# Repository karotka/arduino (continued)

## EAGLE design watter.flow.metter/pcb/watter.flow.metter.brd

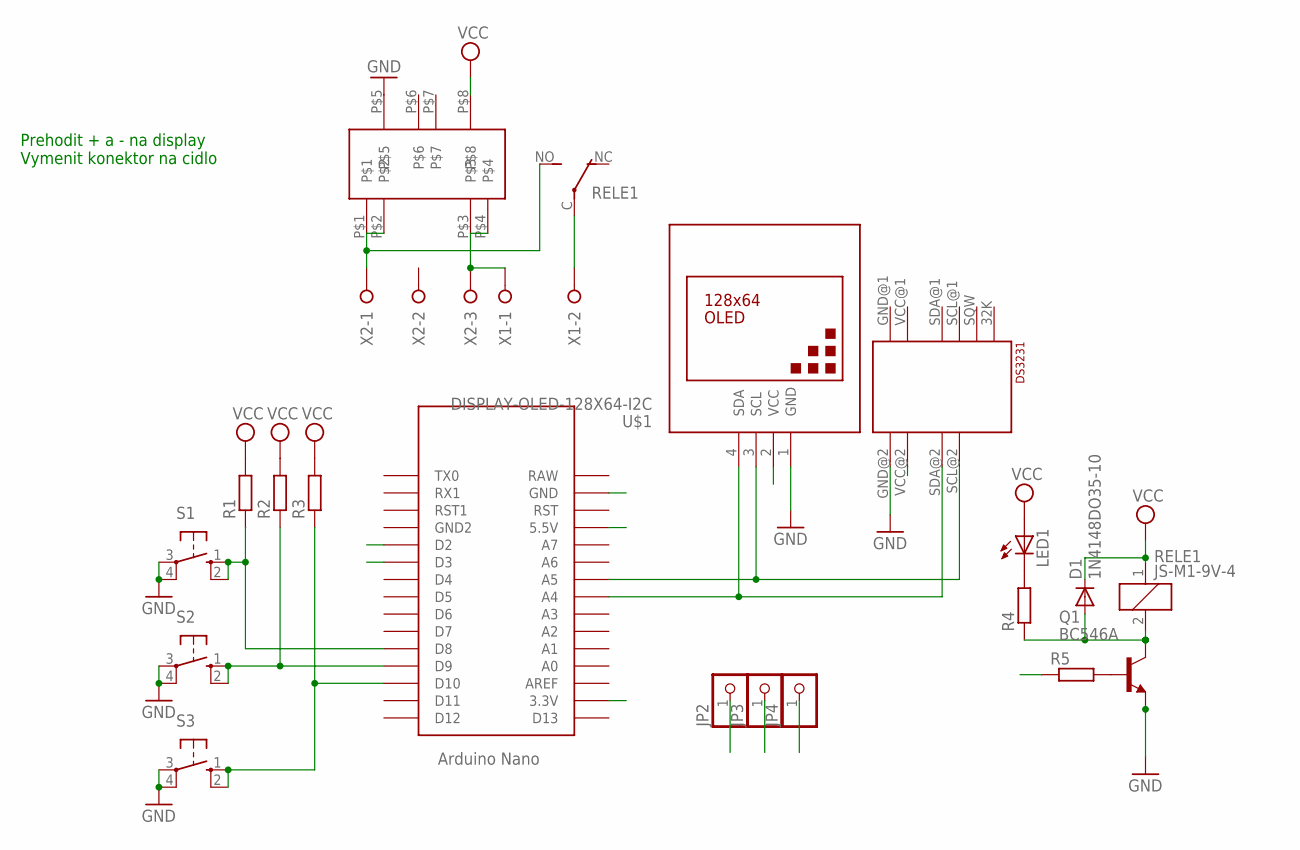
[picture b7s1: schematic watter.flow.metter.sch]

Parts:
D1: 1N4148DO35-10; DO35-10
JP2, JP3, JP4: PINHD-1X1; 1X01
LED1: LED3MM
Q1: BC546A; TO92-EBC
R1, R2, R3, R4: R-EU_0207/10; 0207/10
R5: R-EU_0207/15; 0207/15
RELE1: JS-M1-9V-4; JS-M
S1, S2, S3: 10-XX; B3F-10XX
U$1: DISPLAY-OLED-128X64-I2C
U$2: PWR5V; SUPP
U$5: NANO
U$6: DS3231BOARD; BOARD
X1: W237-02P; W237-132
X2: W237-3E

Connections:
3.3V: U$1.2 (VCC), U$5.3.3V, U$6.VCC@2 (VCC)
D2: JP3.1, U$5.D2
D3: R5.1, U$5.D3
GND: JP4.1, Q1.E, S1.3, S1.4 (P1), S2.3, S2.4 (P1), S3.3, S3.4 (P1), U$1.1 (GND), U$2.P$5, U$5.GND, U$6.GND@1 (GND), U$6.GND@2 (GND)
unnamed: RELE1.C, X1.2
unnamed: R1.1, S1.1 (S), S1.2 (S1), U$5.D8
unnamed: U$2.P$3, U$2.P$4, X1.1, X2.3
unnamed: RELE1.NO (S), U$2.P$1, U$2.P$2, X2.1
unnamed: R2.1, S2.1 (S), S2.2 (S1), U$5.D9
unnamed: R3.1, S3.1 (S), S3.2 (S1), U$5.D10
unnamed: Q1.B, R5.2
unnamed: LED1.K (C), R4.2
unnamed: D1.A, Q1.C, R4.1, RELE1.2
SCL: U$1.3 (SCL), U$5.A5, U$6.SCL@2 (SCL)
SDA: U$1.4 (SDA), U$5.A4, U$6.SDA@2 (SDA)
VCC: D1.C, JP2.1, LED1.A, R1.2, R2.2, R3.2, RELE1.1, U$2.P$8, U$5.5V (5.5V), U$6.VCC@1 (VCC)

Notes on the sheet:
Prehodit + a - na display Vymenit konektor na cidlo

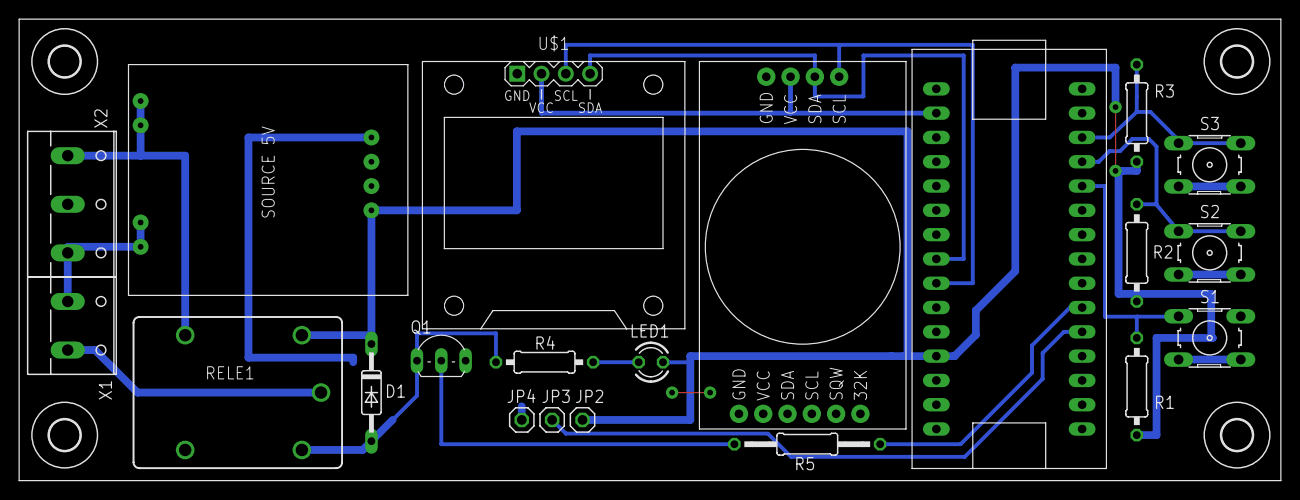
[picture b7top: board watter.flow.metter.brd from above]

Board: 2 copper layers, 131.9 x 48.2 mm, 25 parts (0 on the bottom side), 16 nets.

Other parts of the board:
U$3, U$4, U$7, U$8: 3,2

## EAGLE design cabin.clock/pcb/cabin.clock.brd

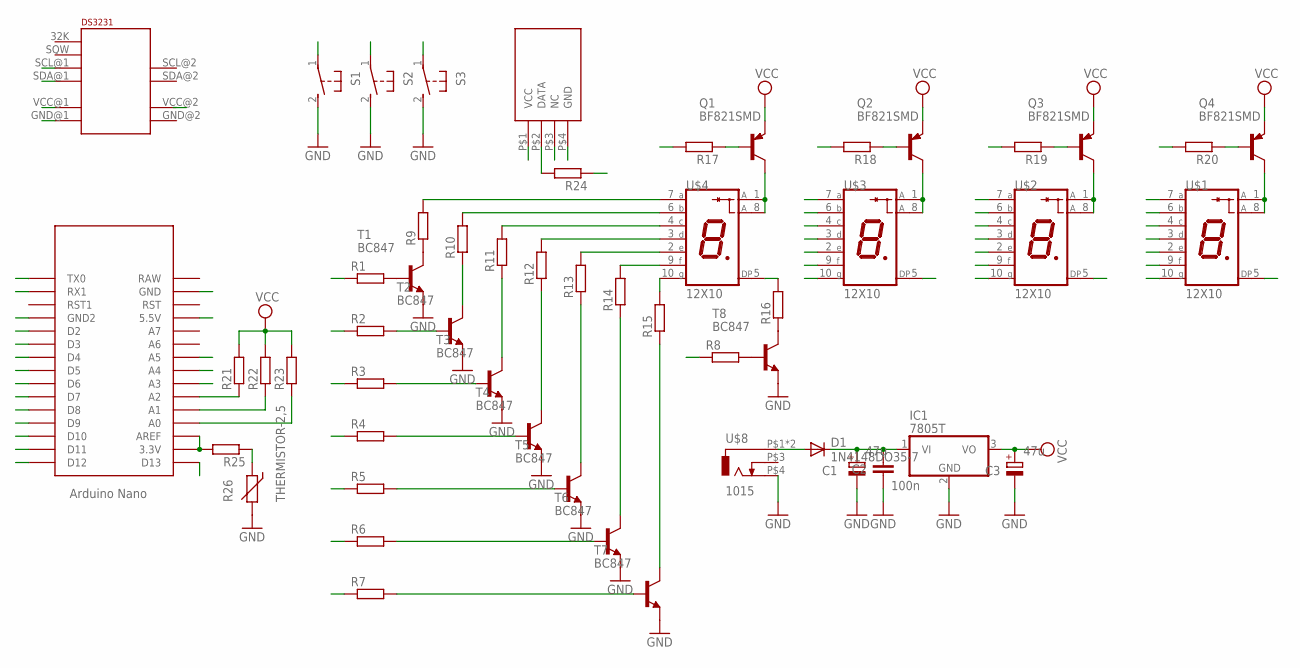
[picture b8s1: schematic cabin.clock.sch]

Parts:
C1, C3: 47u; PANASONIC_D
C2: 100n; C1206
D1: 1N4148DO35-7; DO35-7
IC1: 7805T; TO220H
Q1, Q2, Q3, Q4: BF821SMD; SOT23-BEC
R1, R2, R3, R4, R5, R6, R7, R8, R9, R10, R11, R12, R13, R14, R15, R16, R17, R18, R19, R20, R21, R22, R23, R24, R25: R-EU_0207/10; 0207/10
R26: THERMISTOR-2,5; RS-2,5
S1, S2, S3: 31-XX; B3F-31XX
T1, T2, T3, T4, T5, T6, T7, T8: BC847; SOT23
U$1, U$2, U$3, U$4: 12X10
U$5: NANO
U$6: DS3231BOARD; BOARD
U$7: DTH21
U$8: 1015; 1505

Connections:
A: R9.2, U$1.7 (A), U$2.7 (A), U$3.7 (A), U$4.7 (A)
A0: R23.1, S1.1, U$5.A0
A1: R22.1, S2.1, U$5.A1
A2: R21.1, S3.1, U$5.A2
A3: R25.1, R26.1, U$5.A3
B: R10.2, U$1.6 (B), U$2.6 (B), U$3.6 (B), U$4.6 (B)
C: R11.2, U$1.4 (C), U$2.4 (C), U$3.4 (C), U$4.4 (C)
D: R12.2, U$1.3 (D), U$2.3 (D), U$3.3 (D), U$4.3 (D)
D2: R3.1, U$5.D2
D3: R4.1, U$5.D3
D4: R5.1, U$5.D4
D5: R6.1, U$5.D5
D6: R7.1, U$5.D6
D7: R8.1, U$5.D7
D8: R17.2, U$5.D8
D9: R18.2, U$5.D9
D10: R19.2, U$5.D10
D11: R20.2, U$5.D11
D12: U$5.D12
D13: R24.2, U$5.D13, U$7.P$2 (DATA)
DP: R16.2, U$1.5 (DP), U$2.5 (DP), U$3.5 (DP), U$4.5 (DP)
E: R13.2, U$1.2 (E), U$2.2 (E), U$3.2 (E), U$4.2 (E)
F: R14.2, U$1.9 (F), U$2.9 (F), U$3.9 (F), U$4.9 (F)
G: R15.2, U$1.10 (G), U$2.10 (G), U$3.10 (G), U$4.10 (G)
GND: C1.-, C2.2, C3.-, IC1.2 (GND), R26.2, S1.2 (S), S2.2 (S), S3.2 (S), T1.2 (E), T2.2 (E), T3.2 (E), T4.2 (E), T5.2 (E), T6.2 (E), T7.2 (E), T8.2 (E), U$5.GND, U$5.GND1 (GND2), U$6.GND@1 (GND), U$6.GND@2 (GND), U$7.P$4 (GND), U$8.P$4 (3)
unnamed: R1.2, T1.1 (B)
unnamed: R8.2, T8.1 (B)
unnamed: Q4.C, U$1.1 (A), U$1.8 (A)
unnamed: R9.1, T1.3 (C)
unnamed: Q3.C, U$2.1 (A), U$2.8 (A)
unnamed: R16.1, T8.3 (C)
unnamed: Q2.C, U$3.1 (A), U$3.8 (A)
unnamed: Q1.C, U$4.1 (A), U$4.8 (A)
unnamed: Q1.B, R17.1
unnamed: Q2.B, R18.1
unnamed: Q3.B, R19.1
unnamed: Q4.B, R20.1
unnamed: D1.A, U$8.P$1 (1), U$8.P$2 (1)
unnamed: R25.2, U$5.3.3V, U$5.AREF
unnamed: R10.1, T2.3 (C)
unnamed: R11.1, T3.3 (C)
unnamed: R12.1, T4.3 (C)
unnamed: R13.1, T5.3 (C)
unnamed: R14.1, T6.3 (C)
unnamed: R15.1, T7.3 (C)
unnamed: R2.2, T2.1 (B)
unnamed: R3.2, T3.1 (B)
unnamed: R4.2, T4.1 (B)
unnamed: R5.2, T5.1 (B)
unnamed: R6.2, T6.1 (B)
unnamed: R7.2, T7.1 (B)
RX1: R1.1, U$5.RX1
SCL: U$5.A5, U$6.SCL@1 (SCL)
SDA: U$5.A4, U$6.SDA@1 (SDA)
TX0: R2.1, U$5.TX0
VCC: C3.+, IC1.3 (VO), R21.2, R22.2, R23.2, R24.1, U$5.5V (5.5V), U$6.VCC@1 (VCC), U$7.P$1 (VCC)
VIN: C1.+, C2.1, D1.C, IC1.1 (VI), Q1.E, Q2.E, Q3.E, Q4.E, U$6.VCC@2 (VCC)

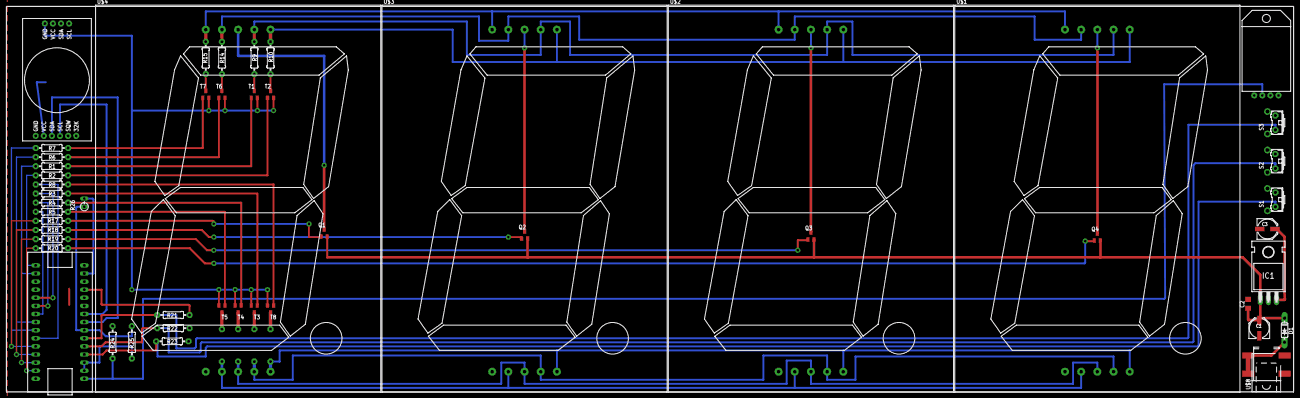
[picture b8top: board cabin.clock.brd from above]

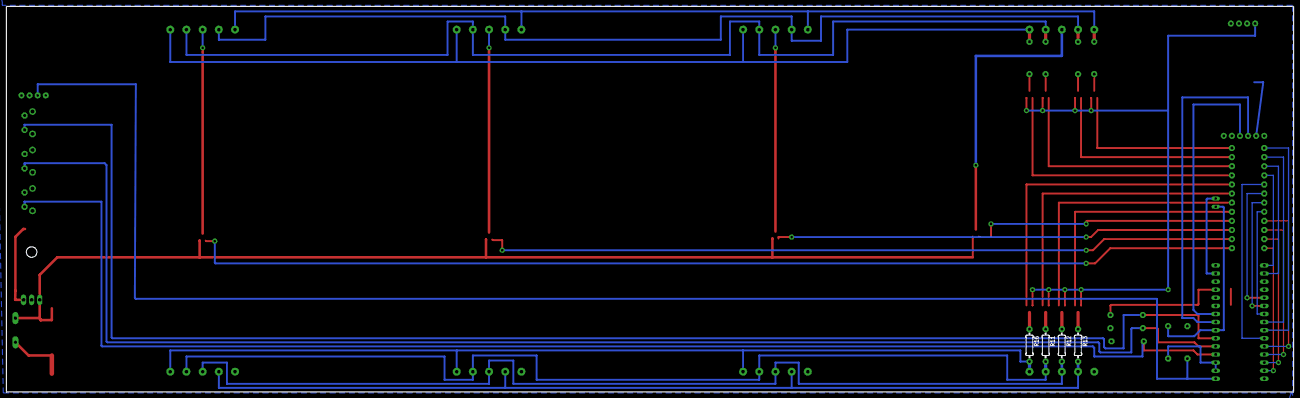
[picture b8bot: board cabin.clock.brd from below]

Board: 2 copper layers, 403.8 x 121.0 mm, 54 parts (4 on the bottom side), 56 nets.

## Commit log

2016-06-30 add time
2016-06-30 add rtc time
2016-07-01 add timer
2016-07-07 chart
2016-07-08 some optimalization
2016-07-10 add pcb
2016-07-14 extension board modified
2016-07-15 add temperature reading
2016-07-19 add thermistor
2016-07-20 fix button local colors
2016-07-26 modified for makefile https://github.com/sudar/Arduino-Makefile
2016-08-24 some text correction
2016-08-25 add libs
2016-09-16 modified to light values
2016-09-16 freeze
2016-09-16 dimming
2016-09-21 test dimming
2016-09-21 dimming by timer for all ready
2016-09-26 first stable
2016-10-03 add 8 time choises
2016-10-03 add readme and bug fixes
2016-11-13 arduino nano clock
2016-11-14 clock setting done
2016-11-16 simple dimmer
2016-11-18 add average dimmer
2016-11-19 divider bug fixed
2016-11-25 fix millis bug
2016-11-27 hvezda
2017-07-24 matric clock prototype with simple dimmer
2017-07-30 clock with dimmer and date switching
2017-08-05 watter flow matter witch display first version
2017-08-12 add timer for periodical switching relay
2017-08-19 add laser cut dwg files
2017-11-07 add scoretable
2017-11-16 add terminal
2017-11-16 add workshop arduino
2018-01-10 optimize touch
2018-01-10 faster loop
2018-05-26 add automatic feeding control
2018-07-29 version 3 done
2018-08-07 version 3
2018-08-07 esp proto
2018-08-15 http first
2018-08-21 new design
2018-08-21 readme
2018-08-21 screenshots
2018-08-31 version 3 first prototype of serial communication
2018-08-31 remove img
2018-08-31 new version
2018-09-03 to be shure
2018-10-17 landscape
2018-10-19 first resp. version
2018-10-24 add first android version
2018-12-21 add heating regulator
2019-05-12 add deep sleep mode
2020-06-09 32 version
2020-06-09 init
2020-06-10 board
2020-06-26 buttons
2020-06-26 add aqua lcd node mcu 32
2020-11-11 first
2020-11-14 time
2020-11-21 time setup
2020-12-18 posledni verze
2021-01-30 esp wifi settings init
2021-02-02 examples
